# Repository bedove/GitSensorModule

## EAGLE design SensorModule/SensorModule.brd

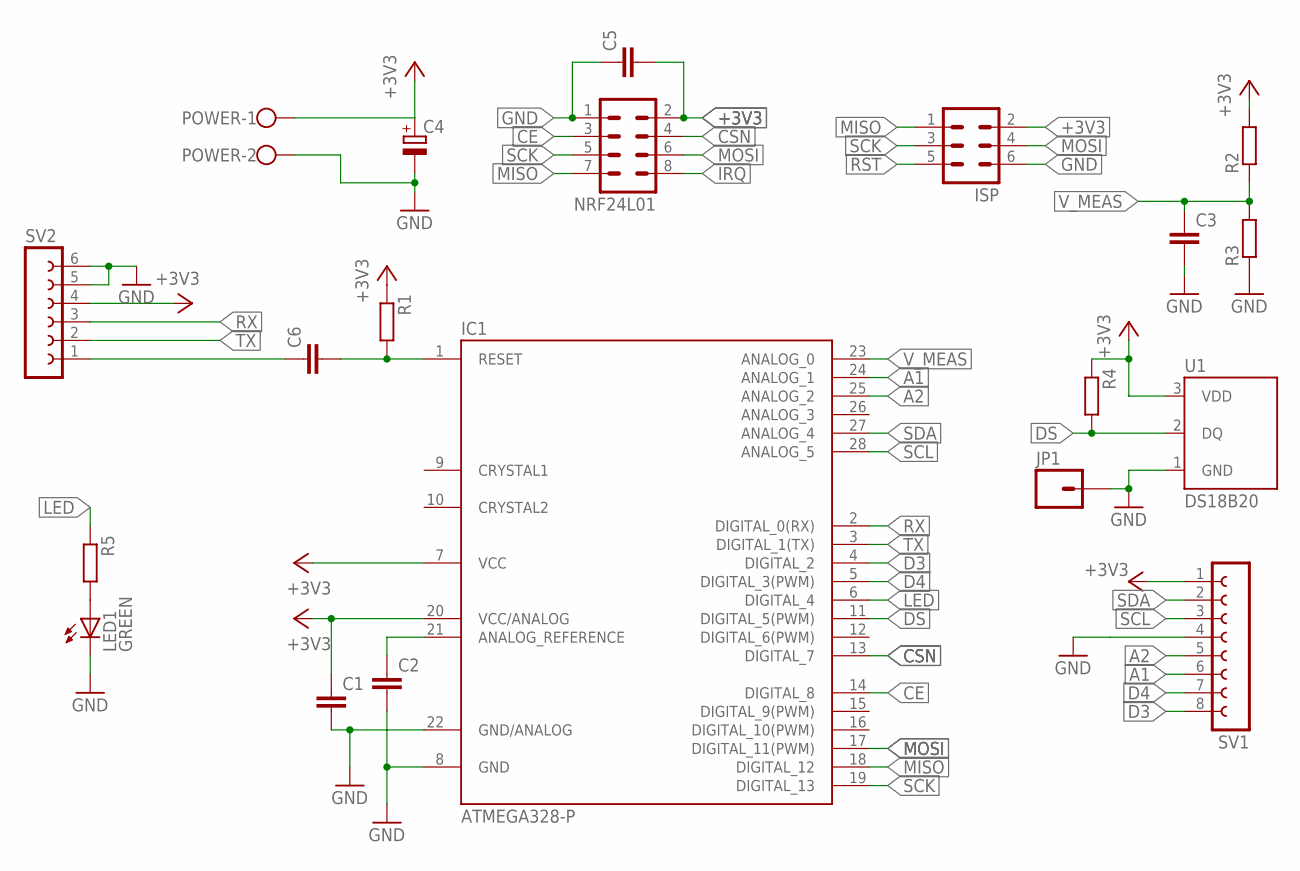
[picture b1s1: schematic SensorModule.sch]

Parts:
C1, C2, C3, C5, C6: C-EU025-025X050; C025-025X050
C4: CPOL-EUE2.5-5; E2,5-5
IC1: ATMEGA328-P; DIL28-3
ISP: MA03-2
JP1: M01PTH_LONGPAD; 1X01_LONGPAD
LED1: GREEN; LED5MM
NRF24L01: MA04-2
POWER: W237-102
R1, R2, R3, R4, R5: R-EU_0204/2V; 0204V
SV1: FE08-1; FE08
SV2: FE06-1; FE06
U1: DS18B20; TO-92-AMMO

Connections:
+3V3: C1.1, C4.+, C5.2, IC1.7 (VCC), IC1.20 (VCC/ANALOG), ISP.2, NRF24L01.2, POWER.1, R1.1, R2.2, R4.1, SV1.1, SV2.4, U1.3 (VDD)
A1: IC1.24 (ANALOG_1), SV1.6
A2: IC1.25 (ANALOG_2), SV1.5
CE: IC1.14 (DIGITAL_8), NRF24L01.3
CSN: IC1.13 (DIGITAL_7), NRF24L01.4
D3: IC1.4 (DIGITAL_2), SV1.8
D4: IC1.5 (DIGITAL_3(PWM)), SV1.7
DS: IC1.11 (DIGITAL_5(PWM)), R4.2, U1.2 (DQ)
GND: C1.2, C2.2, C3.2, C4.-, C5.1, IC1.8 (GND), IC1.22 (GND/ANALOG), ISP.6, JP1.1, LED1.K (C), NRF24L01.1, POWER.2, R3.1, SV1.4, SV2.5, SV2.6, U1.1 (GND)
IRQ: NRF24L01.8
LED: IC1.6 (DIGITAL_4), R5.1
MISO: IC1.18 (DIGITAL_12), ISP.1, NRF24L01.7
MOSI: IC1.17 (DIGITAL_11(PWM)), ISP.4, NRF24L01.6
unnamed: C6.2, IC1.1 (RESET), R1.2
unnamed: C2.1, IC1.21 (ANALOG_REFERENCE)
unnamed: C6.1, SV2.1
unnamed: LED1.A, R5.2
RST: ISP.5
RX: IC1.2 (DIGITAL_0(RX)), SV2.3
SCK: IC1.19 (DIGITAL_13), ISP.3, NRF24L01.5
SCL: IC1.28 (ANALOG_5), SV1.3
SDA: IC1.27 (ANALOG_4), SV1.2
TX: IC1.3 (DIGITAL_1(TX)), SV2.2
V_MEAS: C3.1, IC1.23 (ANALOG_0), R2.1, R3.2

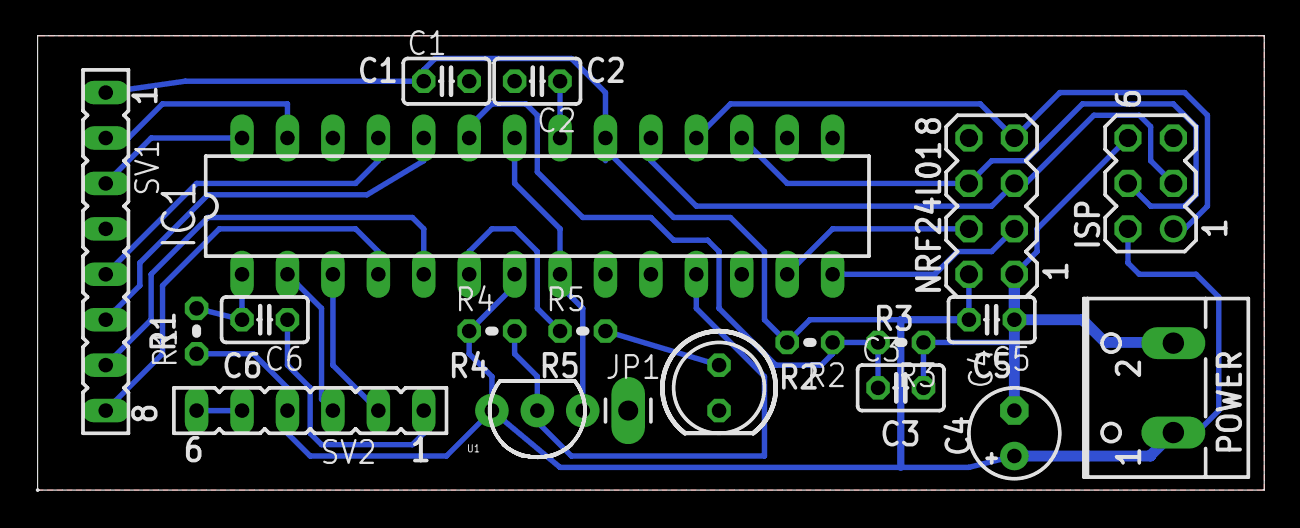
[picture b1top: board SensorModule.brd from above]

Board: 2 copper layers, 68.5 x 25.3 mm, 20 parts (0 on the bottom side), 22 nets.

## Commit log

2015-12-21 :circus_tent: Added .gitattributes
2015-12-21 Initial copy from TempModule_R1A02

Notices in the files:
parts and their libraries:
SparkFun-Sensors: Licensing: Creative Commons ShareAlike 4.0 International - https://creativecommons.org/licenses/by-sa/4.0
